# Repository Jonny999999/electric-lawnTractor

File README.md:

# Throttle Tune – Throttle Adapter for BLDC Motor Controllers

A microcontroller-based board with a PWM-based analog output (RC filter + buffer) to emulate a DAC.
The goal is to improve throttle response and add configurable driving modes to cheap BLDC motor controllers (e.g. 3000 W BLDC "go-kart kit" controllers).  

Currently it is used in the [electric Kettcar conversion](https://pfusch.zone/electric-kettcar.html) with a 3000 W BLDC drive, this board fixes the controller’s unusable throttle mapping and makes the vehicle smooth and controllable adding a lot of flexibility.

*Control box with the custom pcb connected between throttle and motor controller*  
*Contains: PCB, key switch, battery indicator, several UI switches*

---

## Problem

Cheap BLDC controllers (such as KT-style 3000 W kits) have several issues:
- No configuration options at all
- Speed levels provided by the controller are usually defined poorly
- Only ~2 cm (~60 %) of gas pedal travel is actually used
- Jerky, hard-to-control acceleration (tiny pedal movements cause extreme changes in power - positive feedback when accelerating thus pressing the pedal more makes this even worse)

Using only the original setup makes smooth low-speed driving or child-friendly operation nearly impossible

---

## Solution

The **Throttle Tune** board sits between the analog throttle pedal (or handle) and the motor controller.  
It rescales, filters, and manipulates the signal (fading, modes...) while adding safety and convenience features.

---

## Features

### Firmware
- **Throttle remap**: use full pedal range (configure in/out ranges)
- **Ramp-up / fade**: prevents stuttering, smoother control (configurable max rate of change)
- **Speed modes**: 3 levels + hidden "Sport" mode (highly configurable - several parameters on per-mode-basis)
- **Reverse scaling**: reduced throttle in reverse
- **Buzzer alerts**: startup-, reverse-, mode switch beeps

### Hardware
- ATmega8 microcontroller
- Custom DAC output (0–5 V) to motor controller (implementation: PWM output -> lowpass -> buffer)
- CNC-milled single-sided PCB
- Through-hole components (easy to build/repair)
- 3D-printed enclosure
- Inputs: Hall pedal, reverse switch, speed selector
- Outputs: DAC to controller, buzzer

---

## Hardware

### Schematic
[pcb_throttle-tune/export/schematic.pdf](pcb_throttle-tune/export/schematic.pdf)  

### Layout

### PCB Photo

---

## Example Applications

### Electric Kettcar
Documentation: [pfusch.zone/electric-kettcar](https://pfusch.zone/electric-kettcar)

*Wiring of PCB between pedal and controller (right) and the finished vehicle (left).*

---

### Electric Lawn Tractor (temporary use-case)
Documentation: [pfusch.zone/electric-lawn-tractor](https://pfusch.zone/electric-lawn-tractor)

*Throttle Tune board inside in box on top of the motor controller, battery powered (earlier project - initial but temporary use).*

---

## Repository Content
- `pcb_throttle-tune/` – KiCad project, schematic, layout exports
- `fw_throttle-tune/` – AVR firmware (ATmega8)
- `doc/images` – photos of the build and control box

---

## Usage

### Wiring
See [pcb_throttle-tune/export/layout.pdf](pcb_throttle-tune/export/layout.pdf) for what needs to be connected to which terminals.

### Adjust thresholds
Several config options (macro variables) are defined at the top of `main.c` (see detailed comments).
These include controller start/max voltage, pedal min/max voltage, idle voltage, etc.  
To calibrate:  
- Wire everything up  
- Enable `DEBUG_UART_DEBUG_OUTPUT_ENABLED`  
- Build and flash the firmware
- Connect a USB-UART adapter (header pins next to mcu, TX + GND are enough)  
- Play with the throttle and observe the UART logs to determine the values  
- Adjust the macros in `main.c` accordingly, compile, flash, try again

### Configure / Adjust modes
Driving modes are selected via 2 GPIO pins, each with its own config in the `modeConfigs[]` array.  
Parameters can be tuned per mode using this struct:
```c
//=============================
//==== Mode configuration =====
//=============================
typedef struct {
    const char *name;
    uint8_t maxPercent;     // percent of max possible speed applied at full throttle
    uint8_t maxPercentReverse;
    uint8_t beepCount;      // count beeped when entering this mode
    uint16_t rampUpStep;    // max duty increment per interval (max 1023)
    uint16_t rampUpIntervalMs; // note: must be larger than cycle time (consider when UART used alot)
    uint8_t pedalAverageWindowSize; // window size of the moving average to smooth pedal input (0 = disabled)
    // Future: pedal averaging, throttle curve, etc.
} kettcarConfig_t;
```
See comments in main.c and adjust as needed.

### Build & Flash
#### Install Requirements
```bash
yay -S avr-gcc avr-libc make
```

#### Build
```bash
cd fw_throttle-tune/
make
```

#### Flash
Connect avr controller using USBASP V2.0 ISP programmer using the 10pin connector on the pcb
```bash
cd fw_throttle-tune/
make                # compile firmware first
sudo make upload    # flash to MCU via USBasp
```
Note: Be sure to recompile before flashing, or you may upload an old build...

---

## TODO (future hardware rev)
- Add TVS diode  
- Add buzzer footprint (currently wired to spare pin and implemented in firmware, but not documented in pcb design)  
- Drop unused terminals (see notes design)
- Add reverse polarity protection
- Add onboard buck converter to be used with e.g. 72V directly not requiring external converter

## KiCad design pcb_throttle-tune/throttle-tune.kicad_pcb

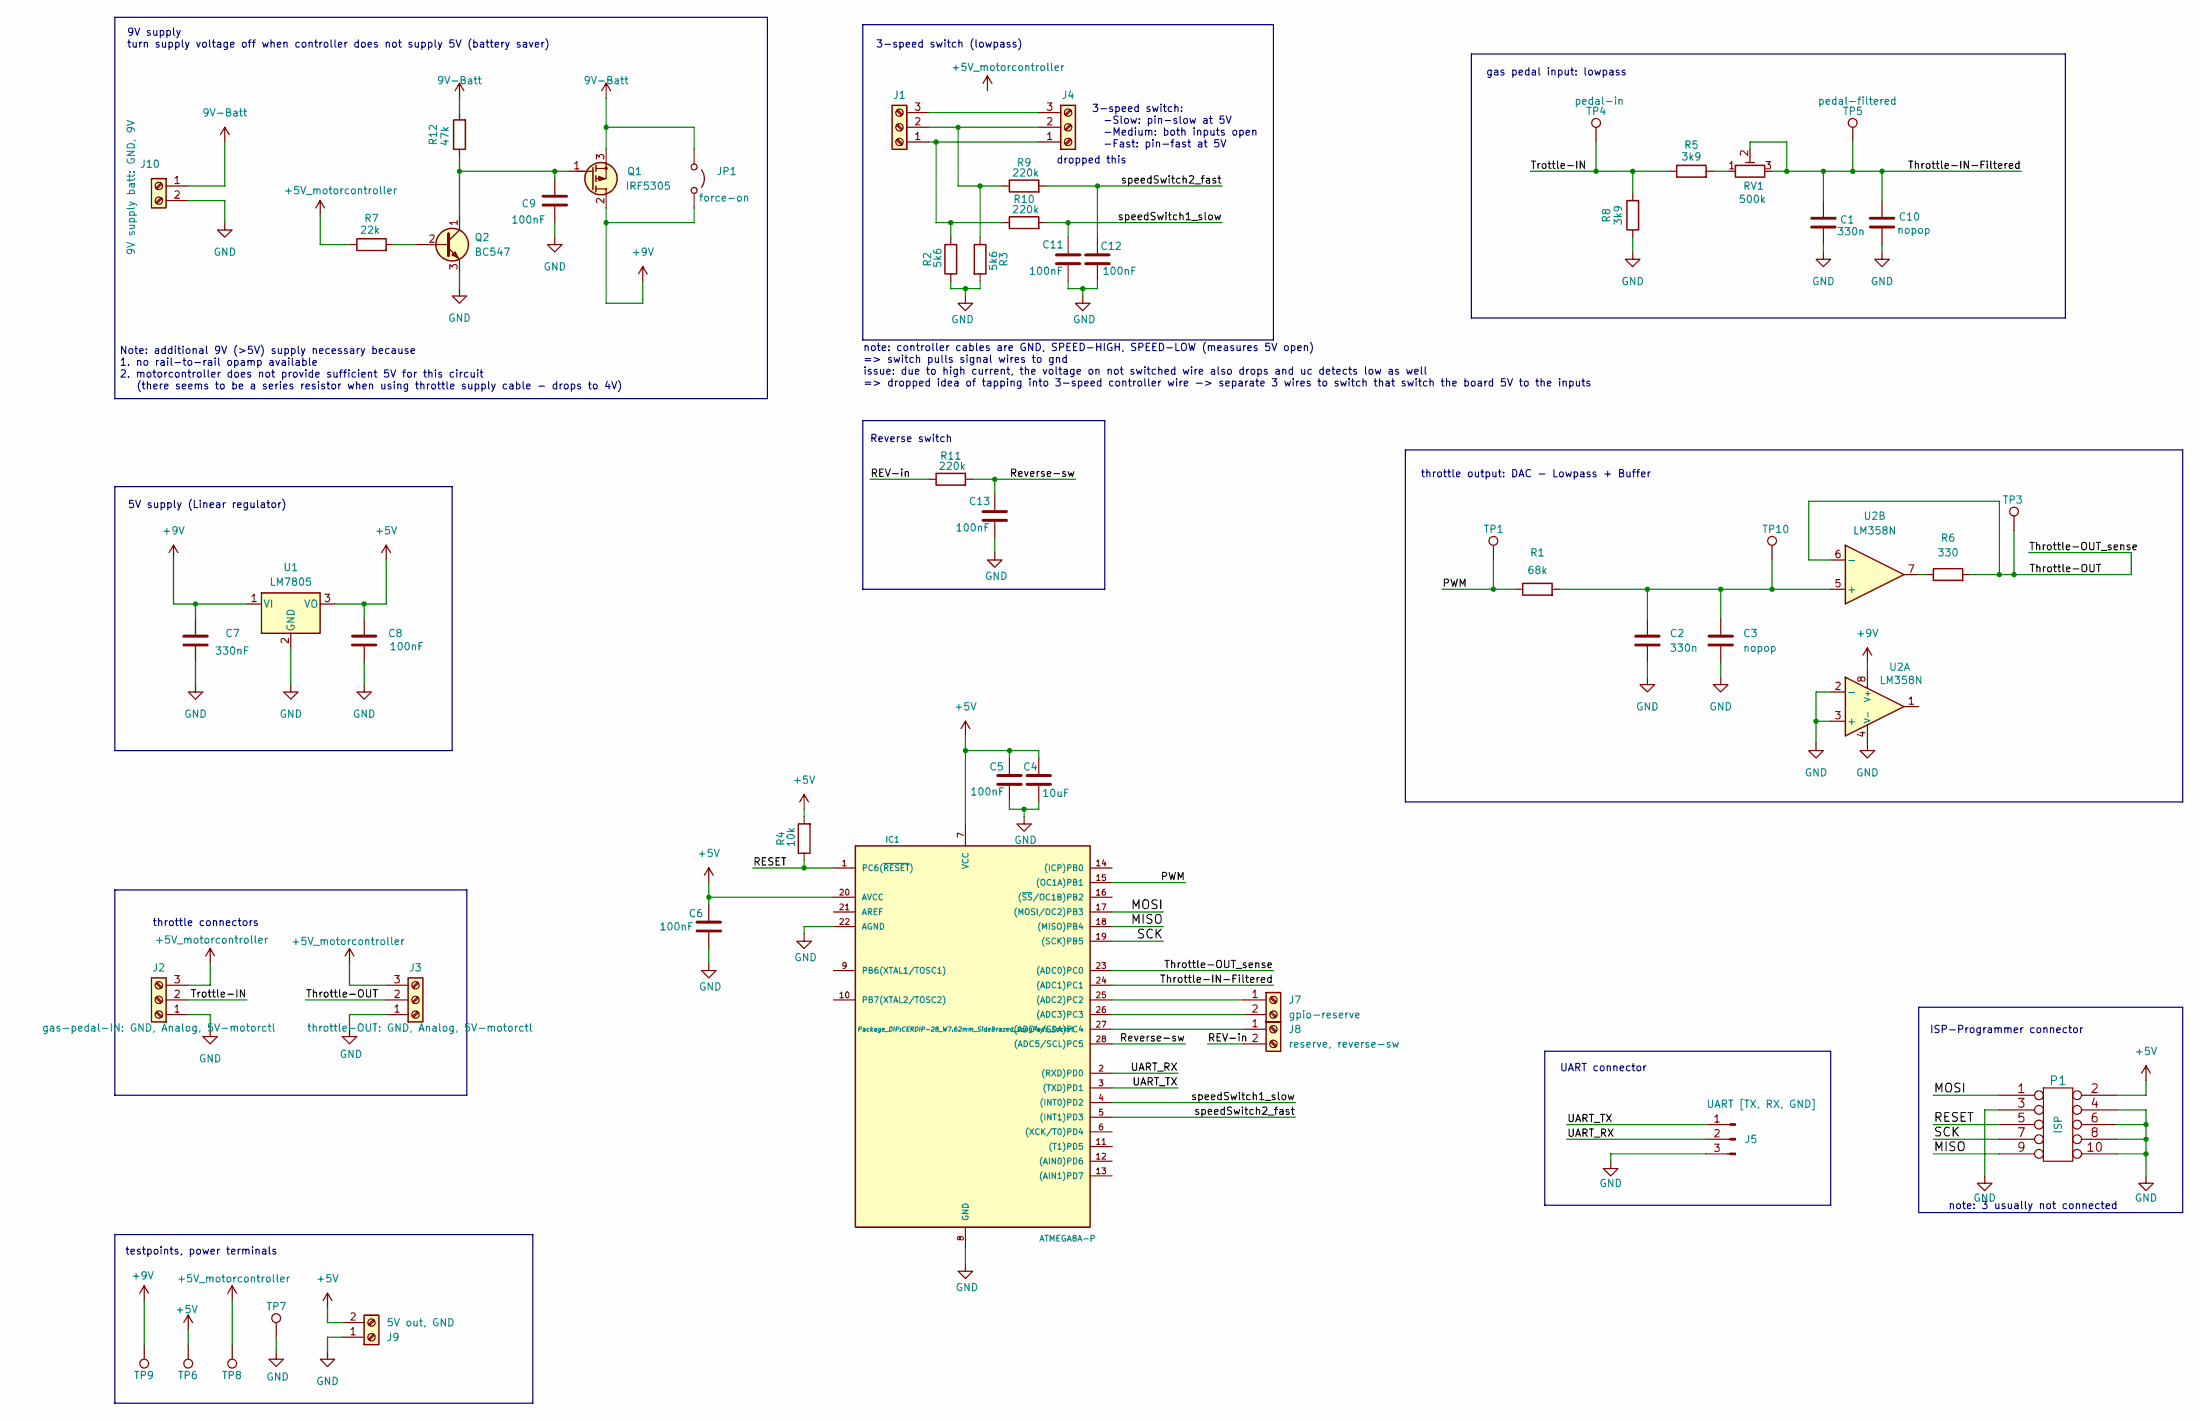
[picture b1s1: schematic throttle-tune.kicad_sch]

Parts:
C1, C2: 330n; C_Disc_D8.0mm_W5.0mm_P5.00mm
C3, C10: nopop; C_Disc_D8.0mm_W5.0mm_P5.00mm
C4: 10uF; CP_Radial_D5.0mm_P2.50mm
C5, C6, C8, C9, C11, C12, C13: 100nF; C_Disc_D7.0mm_W2.5mm_P5.00mm
C7: 330nF; C_Disc_D8.0mm_W5.0mm_P5.00mm
IC1: ATMEGA8A-P; CERDIP-28_W7.62mm_SideBrazed_LongPads_Socket
J1: 3-speed-IN: COM, sw-fast, sw-slow; TerminalBlock_bornier-3_P5.08mm
J2: gas-pedal-IN: GND, Analog, 5V-motorctl; TerminalBlock_bornier-3_P5.08mm
J3: throttle-OUT: GND, Analog, 5V-motorctl; TerminalBlock_bornier-3_P5.08mm
J4: 3-speed-OUT: COM, sw-fast, sw-slow; TerminalBlock_bornier-3_P5.08mm
J5: UART [TX, RX, GND]; PinHeader_1x03_P2.54mm_Vertical
J7: gpio-reserve; TerminalBlock_bornier-2_P5.08mm
J8: reserve, reverse-sw; TerminalBlock_bornier-2_P5.08mm
J9: 5V out, GND; TerminalBlock_bornier-2_P5.08mm
J10: 9V supply batt: GND, 9V; TerminalBlock_bornier-2_P5.08mm
JP1: force-on; Jumper_P2.54mm_D0.7mm
P1: ISP; IDC-Header_2x05_P2.54mm_Vertical
Q1: IRF5305; TO-220-3_Vertical
Q2: BC547; TO-92_Inline_Wide_CBE
R1: 68k; R_Axial_DIN0207_L6.3mm_D2.5mm_P10.16mm_Horizontal
R2, R3: 5k6; R_Axial_DIN0207_L6.3mm_D2.5mm_P10.16mm_Horizontal
R4: 10k; R_Axial_DIN0207_L6.3mm_D2.5mm_P10.16mm_Horizontal
R5, R8: 3k9; R_Axial_DIN0207_L6.3mm_D2.5mm_P10.16mm_Horizontal
R6: 330; R_Axial_DIN0207_L6.3mm_D2.5mm_P10.16mm_Horizontal
R7: 22k; R_Axial_DIN0207_L6.3mm_D2.5mm_P10.16mm_Horizontal
R9, R10, R11: 220k; R_Axial_DIN0207_L6.3mm_D2.5mm_P10.16mm_Horizontal
R12: 47k; R_Axial_DIN0207_L6.3mm_D2.5mm_P10.16mm_Horizontal
RV1: 500k; Potentiometer_Piher_PT-10-V10_Vertical
TP1: PWM; PinHeader_1x01_P1.00mm_Vertical
TP3: Throttle-Out; PinHeader_1x01_P1.00mm_Vertical
TP4: pedal-in; PinHeader_1x01_P1.00mm_Vertical
TP5: pedal-filtered; PinHeader_1x01_P1.00mm_Vertical
TP6: 5V; PinHeader_1x01_P1.00mm_Vertical
TP7: GND; PinHeader_1x01_P1.00mm_Vertical
TP8: 5V controller; PinHeader_1x01_P1.00mm_Vertical
TP9: 9V; PinHeader_1x01_P1.00mm_Vertical
TP10: DAC; PinHeader_1x01_P1.00mm_Vertical
U1: LM7805; TO-220-3_Vertical
U2: LM358N; DIP-8_W7.62mm_LongPads

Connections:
9V-Batt: J10.1, JP1.1 (A), Q1.3 (S), R12.2
+5V: C4.1, C5.1, C6.1, C8.1, IC1.7 (VCC), IC1.20 (AVCC), J9.2, P1.2, R4.2, TP6.1, U1.3 (VO)
+5V_motorcontroller: J2.3, J3.3, R7.1, TP8.1
+9V: C7.1, JP1.2 (B), Q1.2 (D), TP9.1, U1.1 (VI), U2.8 (V+)
/MISO: IC1.18 ((MISO)PB4), P1.9
/MOSI: IC1.17 ((MOSI/OC2)PB3), P1.1
/PWM: IC1.15 ((OC1A)PB1), R1.1, TP1.1
/RESET: IC1.1 (PC6(~RESET)), P1.5, R4.1
/REV-in: J8.2, R11.1
/Reverse-sw: C13.1, IC1.28 ((ADC5/SCL)PC5), R11.2
/SCK: IC1.19 ((SCK)PB5), P1.7
/Throttle-IN-Filtered: C1.1, C10.1, IC1.24 ((ADC1)PC1), RV1.2, RV1.3, TP5.1
/Throttle-OUT: IC1.23 ((ADC0)PC0), J3.2, R6.2, TP3.1, U2.6 (-)
/Trottle-IN: J2.2, R5.1, R8.2, TP4.1
/UART_RX: IC1.2 ((RXD)PD0), J5.2
/UART_TX: IC1.3 ((TXD)PD1), J5.1
/speedSwitch1_slow: C11.1, IC1.4 ((INT0)PD2), R10.2
/speedSwitch2_fast: C12.1, IC1.5 ((INT1)PD3), R9.2
GND: C1.2, C2.2, C3.2, C4.2, C5.2, C6.2, C7.2, C8.2, C9.2, C10.2, C11.2, C12.2, C13.2, IC1.8 (GND), IC1.22 (AGND), J2.1, J3.1, J5.3, J9.1, J10.2, P1.3, P1.4, P1.6, P1.8, P1.10, Q2.3 (E), R2.1, R3.2, R8.1, TP7.1, U1.2 (GND), U2.2 (-), U2.3 (+), U2.4 (V-)
unnamed: IC1.25 ((ADC2)PC2), J7.1
unnamed: IC1.26 ((ADC3)PC3), J7.2
unnamed: IC1.27 ((ADC4/SDA)PC4), J8.1
unnamed: J1.1, J4.1, R2.2, R10.1
unnamed: J1.2, J4.2, R3.1, R9.1
unnamed: J1.3, J4.3
unnamed: C9.1, Q1.1 (G), Q2.1 (C), R12.1
unnamed: Q2.2 (B), R7.2
unnamed: R5.2, RV1.1
unnamed: R6.1, U2.7
unnamed: C2.1, C3.1, R1.2, TP10.1, U2.5 (+)

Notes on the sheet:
throttle output: DAC - Lowpass + Buffer
note: controller cables are GND, SPEED-HIGH, SPEED-LOW (measures 5V open) => switch pulls signal wires to gnd issue: due to high current, the voltage on not switched wire also drops and uc detects low as well => dropped idea of tapping into 3-speed controller wire -> separate 3 wires to switch that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
throttle connectors
UART connector
3-speed switch (lowpass)
9V supply turn supply voltage off when controller does not supply 5V (battery saver)
note: 3 usually not connected
Note: additional 9V (>5V) supply necessary because 1. no rail-to-rail opamp available 2. motorcontroller does not provide sufficient 5V for this circuit (there seems to be a series resistor when using throttle supply cable - drops to 4V)
dropped this
gas pedal input: lowpass
5V supply (Linear regulator)
testpoints, power terminals
ISP-Programmer connector
3-speed switch: -Slow: pin-slow at 5V -Medium: both inputs open -Fast: pin-fast at 5V
Reverse switch

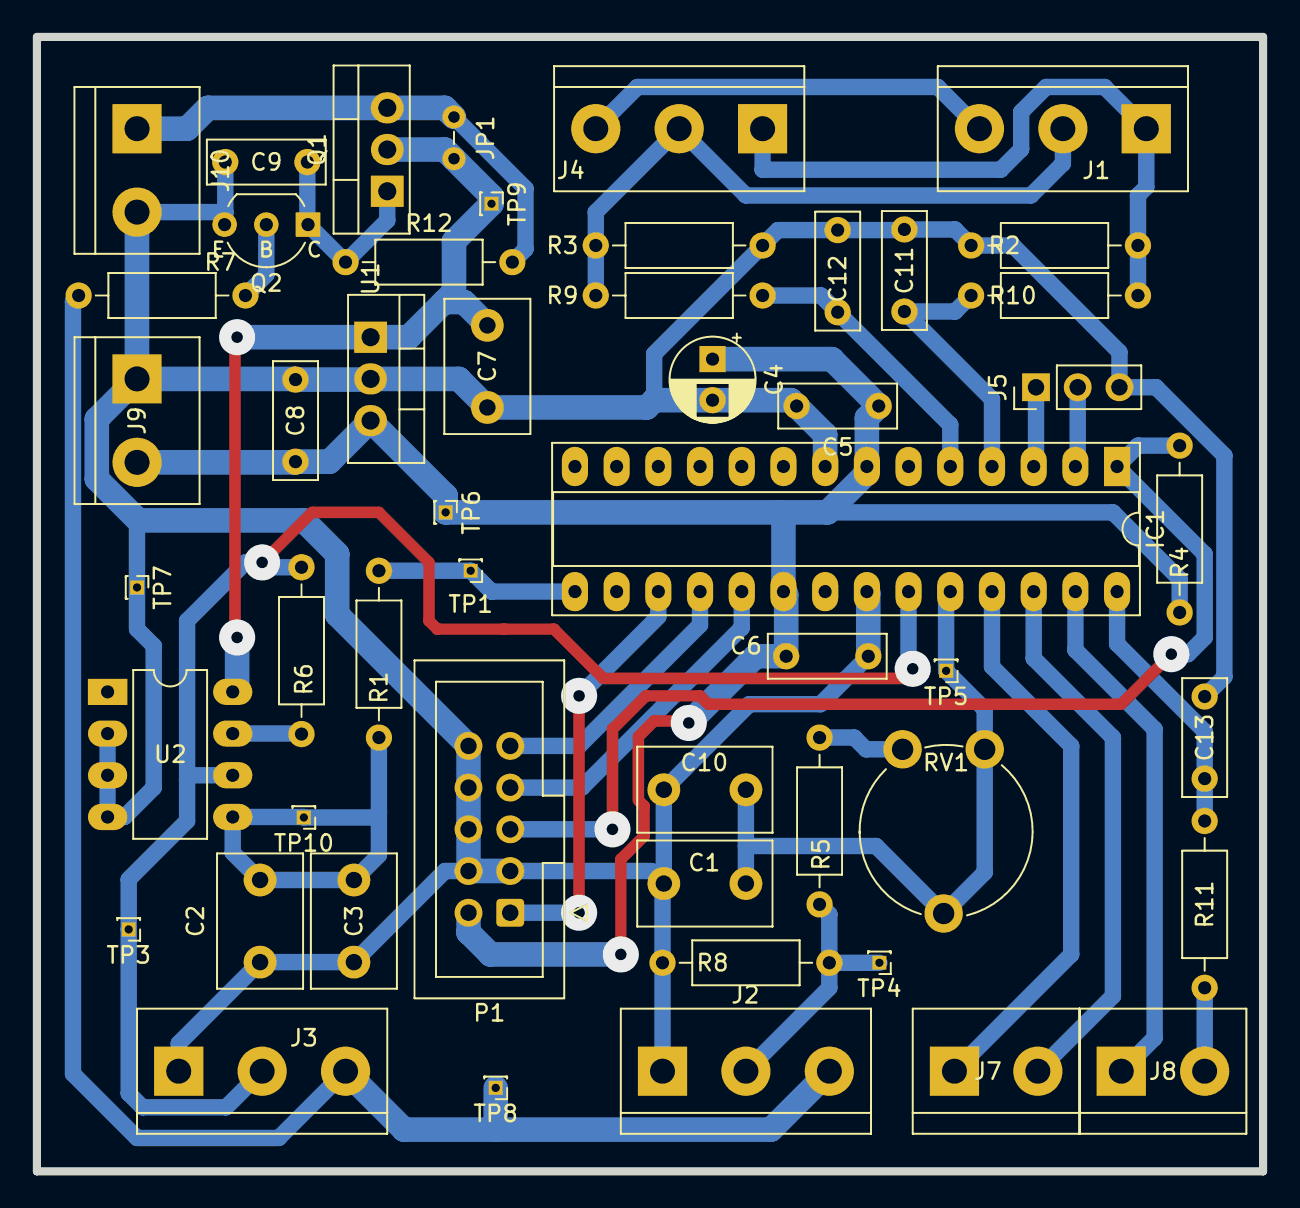
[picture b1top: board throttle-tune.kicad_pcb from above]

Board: 2 copper layers, 74.7 x 69.1 mm, 51 parts (0 on the bottom side), 30 nets.

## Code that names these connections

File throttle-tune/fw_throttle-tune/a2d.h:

#include <util/delay.h>
//#include "bsp_io.h"
//Vcc = 1023
//GND = 0
//
//Atmega8:
//PC5 = ADC5 = Channel 5
//PC4 = ADC4 = Channel 4
//PC3 = ADC2 = Channel 3
//PC2 = ADC2 = Channel 2
//PC1 = ADC1 = Channel 1
//PC0 = ADC0 = Channel 0

//example: value = ReadChannel(5);
uint16_t ReadChannel(uint8_t mux);

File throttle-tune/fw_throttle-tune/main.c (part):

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
//--- configure GPIO Pins ---
// buzzer
const GPIO_Pin buzzerPin = {PC3, &PORTC, &DDRC, &PINC};

// speed switch
const GPIO_Pin speedSwitch_slow = {PD2, &PORTD, &DDRD, &PIND};
const GPIO_Pin speedSwitch_fast = {PD3, &PORTD, &DDRD, &PIND};
const GPIO_Pin reverseSwitch = {PC5, &PORTC, &DDRC, &PINC};



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      timestamp_lastPedalSample = time_get_ms();

      // sample adc - TODO: add multisampling?
      adcInputGasPedal = ReadChannel(1); // PC5

      // calculate gas pedal percentage
      if (adcInputGasPedal <= GAS_PEDAL_MIN)
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    //======================================
#if DEBUG_UART_DEBUG_OUTPUT_ENABLED
    //(generated analog voltage via pwm)
    uint16_t adcOutput = ReadChannel(0); // PC4  - measure generated output voltage for debugging
    // calculate motor percentage from output voltage (for logging)
    uint16_t motorPercent_x10;
    if (adcOutput <= CONTROLLER_START)
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
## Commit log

2024-08-13 Add kicad project for throttle-tune board
2024-08-13 Copy Atmega8 firmware project for throttle-tune board
2024-08-14 Add UART (functional), led blinking
2024-08-14 Add 10Bit Fast-PWM, Add adc
2024-08-14 pcb: schematic using supply motorcontroller (dropped)
2024-08-14 pcb: finish schematic (9V, cut-suppy, filters)
2024-08-14 pcb: arrange components
2024-08-15 Add throttle scaling (works)
2024-08-15 pcb: finish layout, pcb2gcode, adj pins - milled pcb
    milled pcb and populated, works well but
    error with P-channel mosfet (missing NPN driver)
2024-08-15 Rework main.c: Structure, logging, scaling
2024-08-16 pcb: fix supply cutoff (add NPN), update layout
    Note: fixed in already milled pcb by adding transistor with wires
2024-08-16 Add speed-switch support, fading, faster-resume duty
2024-08-20 pcb: optimize text, comments, Add README
2024-08-20 Add Photo of pcb
2024-09-29 Add schematic, 3d-model exports, Assign 3d-models
2025-01-26 Add text annotations for connecting, Update exports
2025-03-22 Add custom gpio lib (copied from ekart project)
2025-03-22 Add buzzer output, beeps at startup
2025-03-23 Replace register access with GPIO lib for speed switch
2025-03-29 Add beeping at speed-sw-change, Outsource functions (beep, speet-sw), Update buzzer pin
2025-04-21 Adjust controller/pedal thresholds for kettcar setup (3000W kit pedal)
2025-04-21 Update Readme: Add tasks for next PCB version
2025-04-22 Add custom time lib (from e-kart proj), Rework fading using timestamps
2025-04-22 Add custom pwm lib (from e-kart proj), Use outsourced pwm functions
2025-04-22 Change to new mode selection approach (Array + outsourced functions), Add sport mode sequence
2025-04-22 Add moving average to pedal input
2025-04-23 Add IDLE-voltage + separate reverse duty, Improve beeping, Adjust speed-level config while testing
2025-04-26 Add pedal sampling interval limit, Optimize avg window conf, Add cycle time logging
2025-04-26 Add spreadsheet for calculating fading options
2025-05-01 Fix debug-output, Add cycle-time results, Adjust pedal, mem, avg options
2025-05-01 Add custom controller-full-speed-duty threshold, Limit UART debug output to 500ms
2025-08-18 Remove unnecessary subfolder
2025-08-18 Add detailed README and photos
2025-08-19 Update README: Add Usage section, Fix link
